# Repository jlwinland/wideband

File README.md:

# wideband
Wideband Controller
Supporting dual LSU 4.9 sensors and based on work by @mck1117

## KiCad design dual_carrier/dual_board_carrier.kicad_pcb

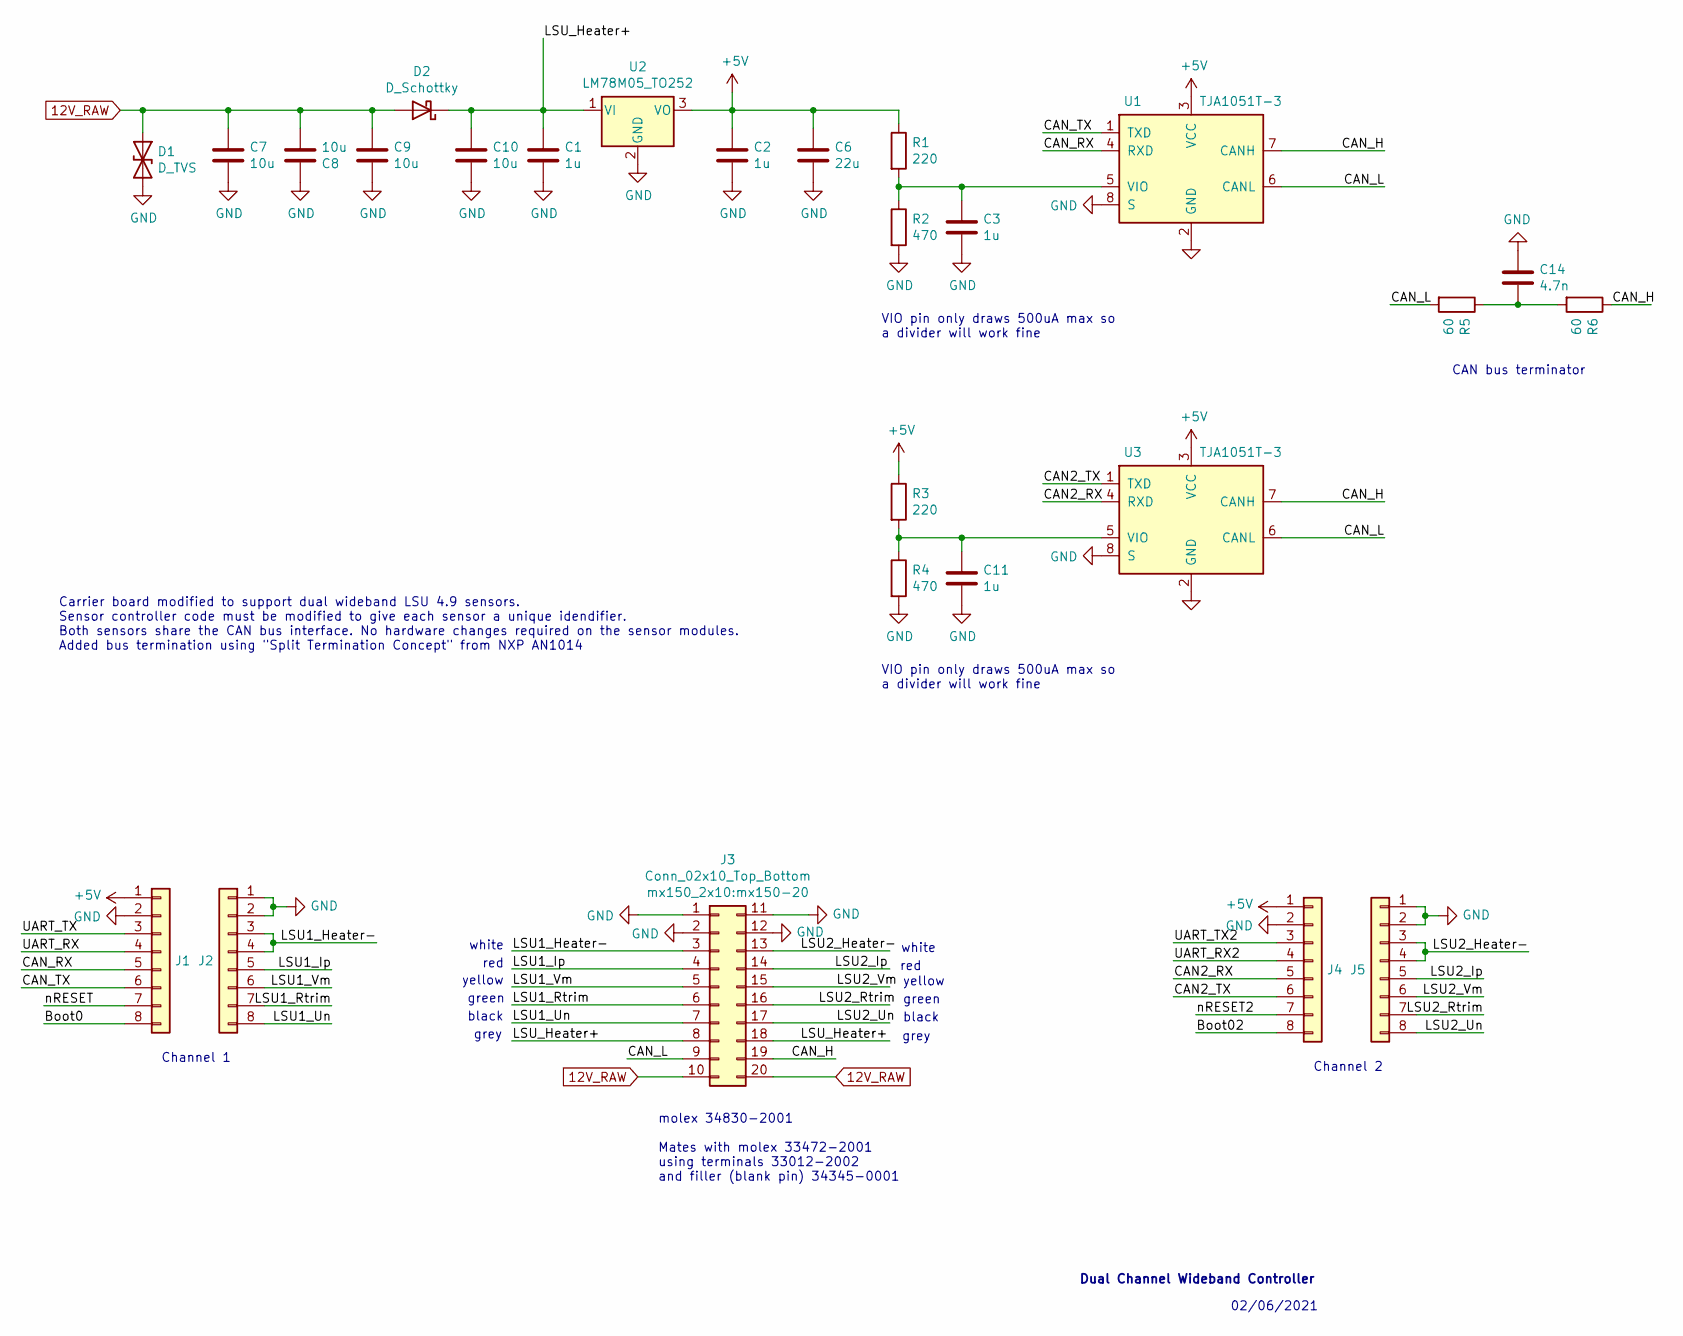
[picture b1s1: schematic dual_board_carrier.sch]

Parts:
C1, C2, C3, C11: 1u; C_0603_1608Metric; LCSC C15849
C6: 22u; C_0805_2012Metric; LCSC C45783
C7, C8, C9, C10: 10u; C_1206_3216Metric; LCSC C13585
C14: 4.7n; C_0603_1608Metric; LCSC C1567
D1: D_TVS; D_SMC; LCSC C151279
D2: D_Schottky; D_SMA; LCSC C22452
J1, J2, J4, J5: Conn_01x08; PinSocket_1x08_P2.54mm_Vertical
J3: Conn_02x10_Top_Bottom; mx150-20
R1, R3: 220; R_0603_1608Metric; LCSC C22962
R2, R4: 470; R_0603_1608Metric; LCSC C23179
R5, R6: 60; R_1206_3216Metric; LCSC C23179
U1, U3: TJA1051T-3; SOIC-8_3.9x4.9mm_P1.27mm; LCSC C38695
U2: LM78M05_TO252; TO-252-2; LCSC C58069

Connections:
12V_RAW: C7.1, C8.2, C9.1, D1.1 (A1), D2.2 (A), J3.10, J3.20
+5V: C2.1, C6.1, J1.1, J4.1, R1.1, R3.1, U1.3 (VCC), U2.3 (VO), U3.3 (VCC)
/Boot0: J1.8
/Boot02: J4.8
/CAN2_RX: J4.5, U3.4 (RXD)
/CAN2_TX: J4.6, U3.1 (TXD)
/CAN_H: J3.19, R6.1, U1.7 (CANH), U3.7 (CANH)
/CAN_L: J3.9, R5.2, U1.6 (CANL), U3.6 (CANL)
/CAN_RX: J1.5, U1.4 (RXD)
/CAN_TX: J1.6, U1.1 (TXD)
/LSU1_Heater-: J2.3, J2.4, J3.3
/LSU1_Ip: J2.5, J3.4
/LSU1_Rtrim: J2.7, J3.6
/LSU1_Un: J2.8, J3.7
/LSU1_Vm: J2.6, J3.5
/LSU2_Heater-: J3.13, J5.3, J5.4
/LSU2_Ip: J3.14, J5.5
/LSU2_Rtrim: J3.16, J5.7
/LSU2_Un: J3.17, J5.8
/LSU2_Vm: J3.15, J5.6
/LSU_Heater+: C1.1, C10.1, D2.1 (K), J3.8, J3.18, U2.1 (VI)
/UART_RX: J1.4
/UART_RX2: J4.4
/UART_TX: J1.3
/UART_TX2: J4.3
/nRESET: J1.7
/nRESET2: J4.7
GND: C1.2, C2.2, C3.2, C6.2, C7.2, C8.1, C9.2, C10.2, C11.2, C14.1, D1.2 (A2), J1.2, J2.1, J2.2, J3.1, J3.2, J3.11, J3.12, J4.2, J5.1, J5.2, R2.2, R4.2, U1.2 (GND), U1.8 (S), U2.2 (GND), U3.2 (GND), U3.8 (S)
unnamed: C3.1, R1.2, R2.1, U1.5 (VIO)
unnamed: C11.1, R3.2, R4.1, U3.5 (VIO)
unnamed: C14.2, R5.1, R6.2

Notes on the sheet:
VIO pin only draws 500uA max so a divider will work fine
black
green
yellow
grey
white
red
Channel 1
Channel 2
molex 34830-2001 Mates with molex 33472-2001 using terminals 33012-2002 and filler (blank pin) 34345-0001
Carrier board modified to support dual wideband LSU 4.9 sensors. Sensor controller code must be modified to give each sensor a unique idendifier. Both sensors share the CAN bus interface. No hardware changes required on the sensor modules. Added bus termination using "Split Termination Concept" fro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
02/06/2021
Dual Channel Wideband Controller
CAN bus terminator

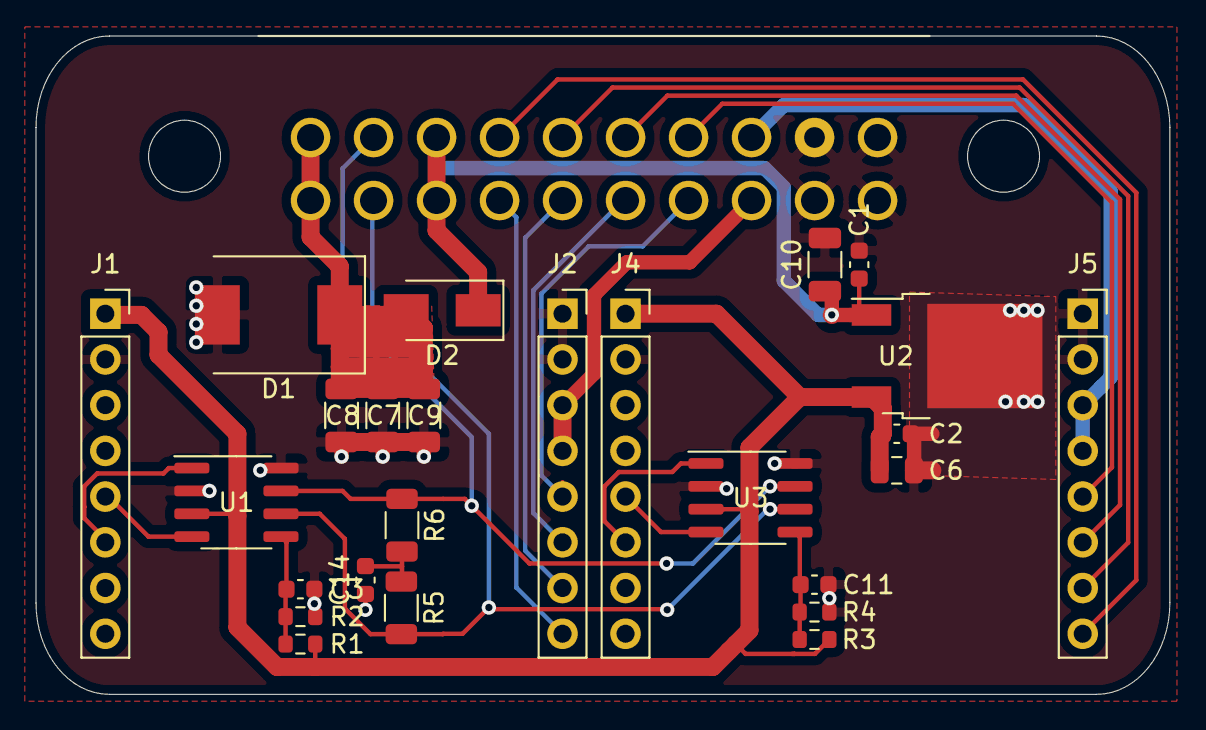
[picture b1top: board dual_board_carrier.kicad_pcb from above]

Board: 2 copper layers, 63.0 x 36.6 mm, 26 parts (0 on the bottom side), 23 nets.

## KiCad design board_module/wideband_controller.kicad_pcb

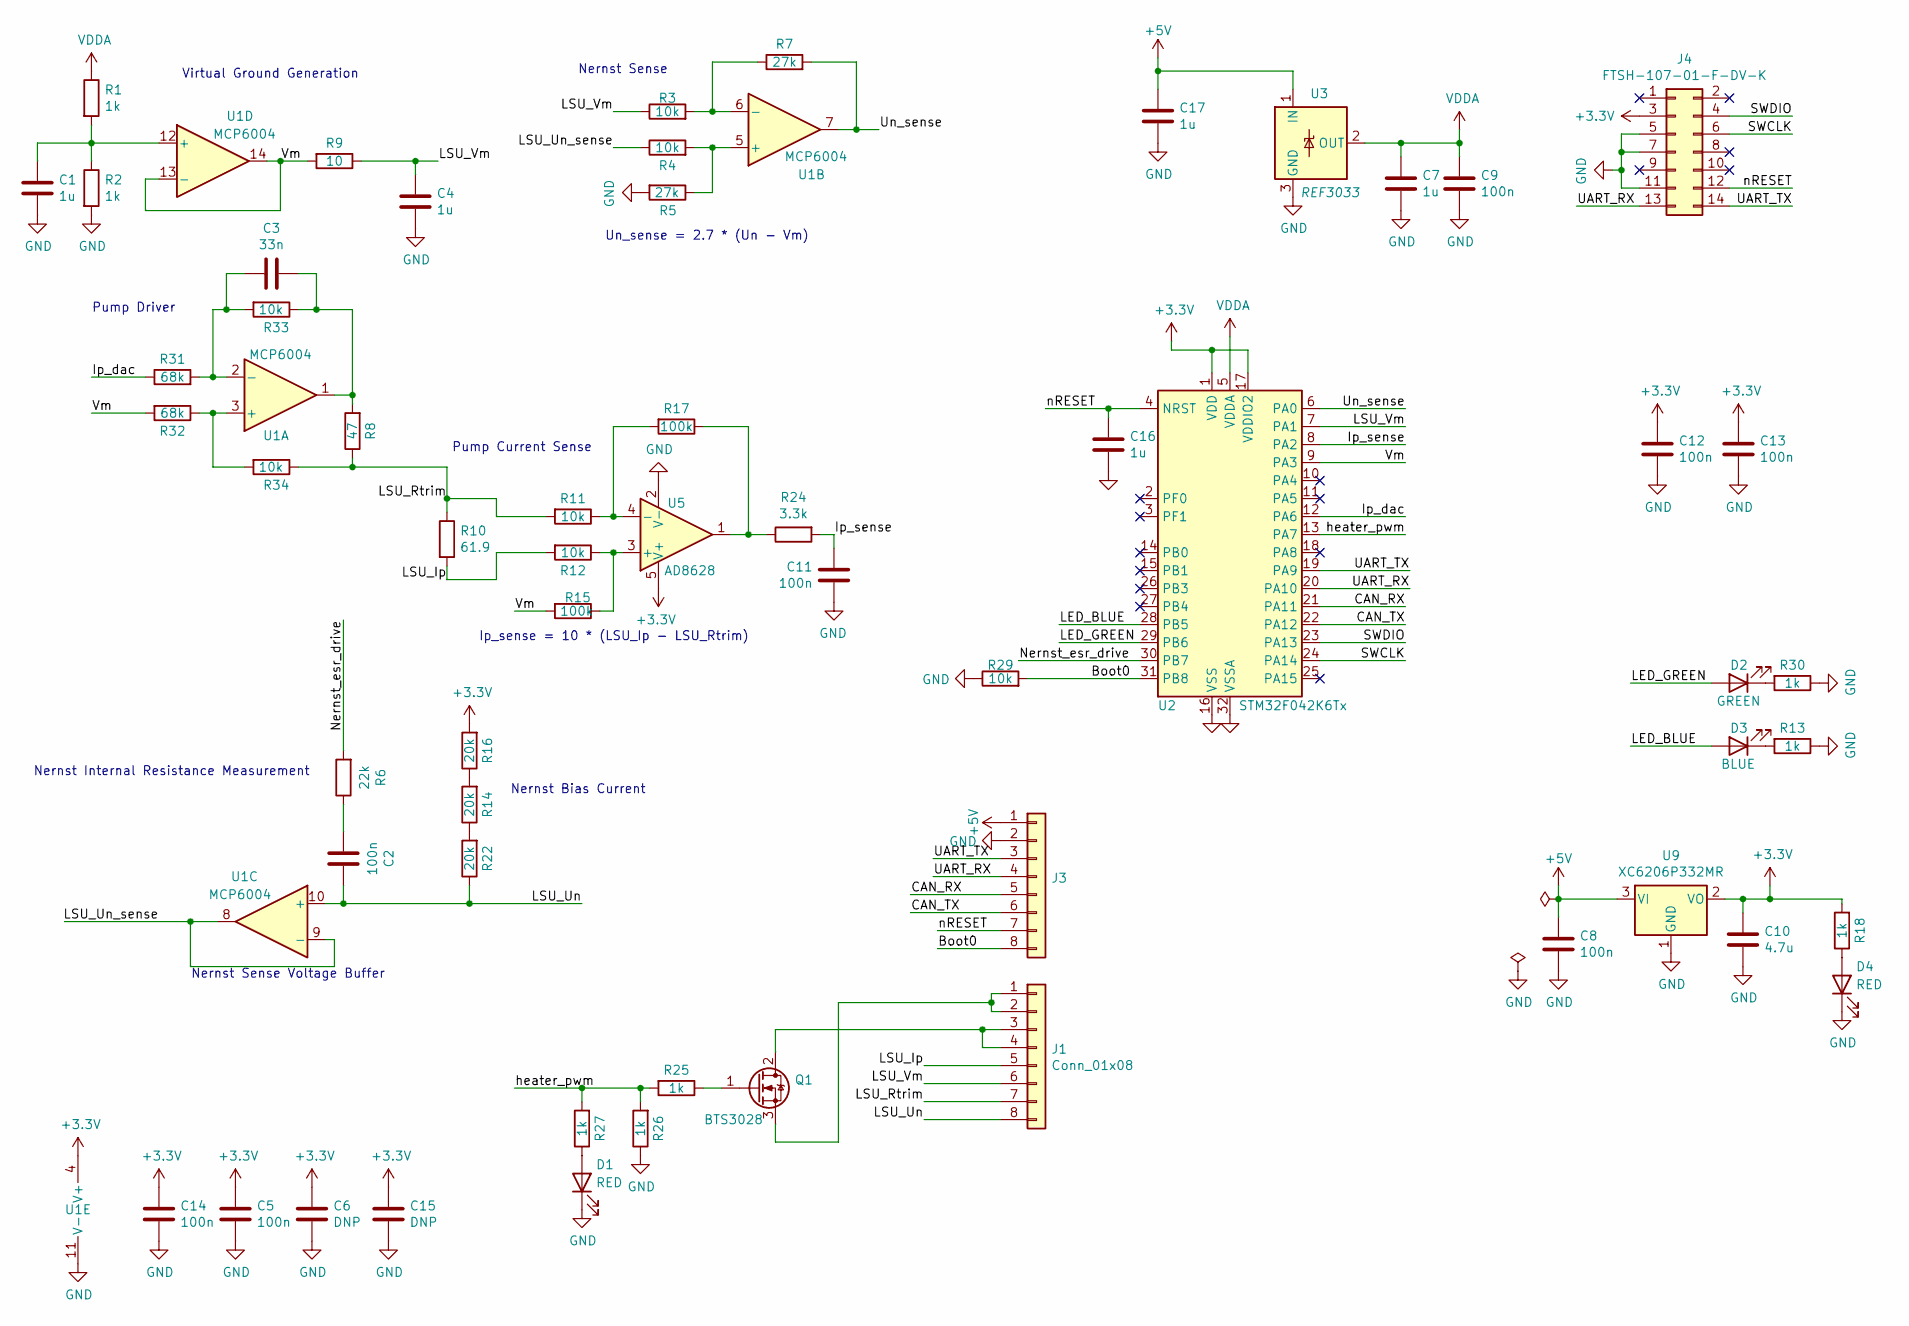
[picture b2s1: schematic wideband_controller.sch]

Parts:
C1, C4, C7, C16, C17: 1u; C_0402_1005Metric; LCSC C52923
C2, C5, C8, C9, C11, C12, C13, C14: 100n; C_0402_1005Metric; LCSC C1525
C3: 33n; C_0402_1005Metric; LCSC C1585
C6, C15: DNP; C_0402_1005Metric
C10: 4.7u; C_0603_1608Metric; LCSC C19666
D1, D4: RED; LED_0603_1608Metric; LCSC C2286
D2: GREEN; LED_0603_1608Metric; LCSC C72043
D3: BLUE; LED_0603_1608Metric; LCSC C72041
J1, J3: Conn_01x08; PinHeader_1x08_P2.54mm_Vertical
J4: FTSH-107-01-F-DV-K; PinHeader_2x07_P1.27mm_Vertical_SMD
Q1: BTS3028; TO-252-2; LCSC C112639
R1, R2, R13, R18, R25, R26, R27, R30: 1k; R_0402_1005Metric; LCSC C11702
R3, R4, R11, R12, R29, R33, R34: 10k; R_0402_1005Metric; LCSC C25744
R5, R7: 27k; R_0402_1005Metric; LCSC C25771
R6: 22k; R_0402_1005Metric; LCSC C25768
R8: 47; R_0402_1005Metric; LCSC C25118
R9: 10; R_0402_1005Metric; LCSC C25077
R10: 61.9; R_0603_1608Metric; LCSC C23092
R14, R16, R22: 20k; R_0402_1005Metric; LCSC C25765
R15, R17: 100k; R_0402_1005Metric; LCSC C25741
R24: 3.3k; R_0402_1005Metric; LCSC C25890
R31, R32: 68k; R_0402_1005Metric; LCSC C36871
U1: MCP6004; TSSOP-14_4.4x5mm_P0.65mm; LCSC C50282
U2: STM32F042K6Tx; LQFP-32_7x7mm_P0.8mm; LCSC C69216
U3: REF3033; SOT-23; LCSC C36658
U5: AD8628; TSOT-23-5; LCSC C29309
U9: XC6206P332MR; SOT-23; LCSC C5446

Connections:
+3V3: C5.1, C6.1, C10.1, C12.1, C13.1, C14.1, C15.1, J4.3, R16.2, R18.2, U1.4 (V+), U2.1 (VDD), U2.17 (VDDIO2), U5.5 (V+), U9.2 (VO)
+5V: C8.1, C17.1, J3.1, U3.1 (IN), U9.3 (VI)
/Boot0: J3.8, R29.2, U2.31 (PB8)
/CAN_RX: J3.5, U2.21 (PA11)
/CAN_TX: J3.6, U2.22 (PA12)
/Ip_dac: R31.1, U2.12 (PA6)
/Ip_sense: C11.1, R24.2, U2.8 (PA2)
/LED_BLUE: D3.2 (A), U2.28 (PB5)
/LED_GREEN: D2.2 (A), U2.29 (PB6)
/LSU_Ip: J1.5, R10.2, R12.2
/LSU_Rtrim: J1.7, R8.1, R10.1, R11.2, R34.1
/LSU_Un: C2.1, J1.8, R22.1, U1.10 (+)
/LSU_Un_sense: R4.1, U1.8, U1.9 (-)
/LSU_Vm: C4.1, J1.6, R3.1, R9.1, U2.7 (PA1)
/Nernst_esr_drive: R6.2, U2.30 (PB7)
/SWCLK: J4.6, U2.24 (PA14)
/SWDIO: J4.4, U2.23 (PA13)
/UART_RX: J3.4, J4.13, U2.20 (PA10)
/UART_TX: J3.3, J4.14, U2.19 (PA9)
/Un_sense: R7.2, U1.7, U2.6 (PA0)
/Vm: R9.2, R15.2, R32.2, U1.13 (-), U1.14, U2.9 (PA3)
/heater_pwm: R25.2, R26.2, R27.2, U2.13 (PA7)
/nRESET: C16.1, J3.7, J4.12, U2.4 (NRST)
GND: C1.2, C4.2, C5.2, C6.2, C7.2, C8.2, C9.2, C10.2, C11.2, C12.2, C13.2, C14.2, C15.2, C16.2, C17.2, D1.1 (K), D4.1 (K), J3.2, J4.5, J4.7, J4.11, R2.2, R5.2, R13.1, R26.1, R29.1, R30.1, U1.11 (V-), U2.16 (VSS), U2.32 (VSSA), U3.3 (GND), U5.2 (V-), U9.1 (GND)
unnamed: C1.1, R1.2, R2.1, U1.12 (+)
unnamed: C2.2, R6.1
unnamed: C3.1, R8.2, R33.1, U1.1
unnamed: C3.2, R31.2, R33.2, U1.2 (-)
unnamed: D1.2 (A), R27.1
unnamed: D2.1 (K), R30.2
unnamed: D3.1 (K), R13.2
unnamed: D4.2 (A), R18.1
unnamed: J1.1, J1.2, Q1.3 (S)
unnamed: J1.3, J1.4, Q1.2 (D)
unnamed: Q1.1 (G), R25.1
unnamed: R3.2, R7.1, U1.6 (-)
unnamed: R4.2, R5.1, U1.5 (+)
unnamed: R11.1, R17.2, U5.4 (-)
unnamed: R12.1, R15.1, U5.3 (+)
unnamed: R14.1, R22.2
unnamed: R14.2, R16.1
unnamed: R17.1, R24.1, U5.1
unnamed: R32.1, R34.2, U1.3 (+)
VDDA: C7.1, C9.1, R1.1, U2.5 (VDDA), U3.2 (OUT)

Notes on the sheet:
Pump Current Sense
Virtual Ground Generation
Nernst Internal Resistance Measurement
Pump Driver
Nernst Sense
Un_sense = 2.7 * (Un - Vm)
Ip_sense = 10 * (LSU_Ip - LSU_Rtrim)
Nernst Sense Voltage Buffer
Nernst Bias Current

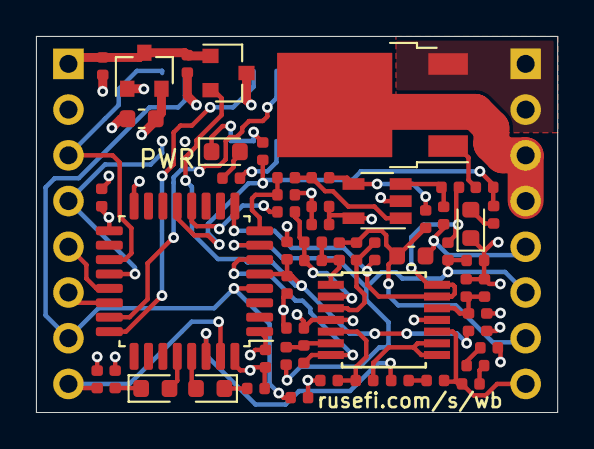
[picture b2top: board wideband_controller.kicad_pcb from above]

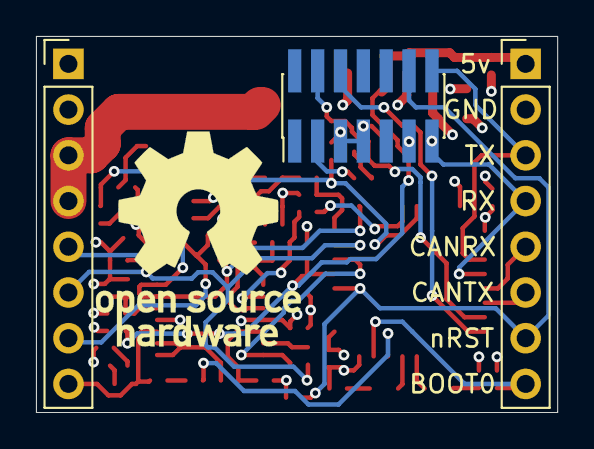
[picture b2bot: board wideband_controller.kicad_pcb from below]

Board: 4 copper layers, 29.0 x 20.9 mm, 59 parts (3 on the bottom side), 44 nets.

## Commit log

2021-01-23 Dual Carrier v0.1
2021-01-29 Add files via upload
    Dual Carrier v0.2
2021-02-08 Add files via upload
    02/07/21 Updates to dual_carrier and creation of dual_carrier_sxs
